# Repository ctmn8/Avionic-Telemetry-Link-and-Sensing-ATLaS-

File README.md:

# Avionic-Telemetry-Link-and-Sensing-ATLaS-
All-in-one telemetry system designed for rocketry.

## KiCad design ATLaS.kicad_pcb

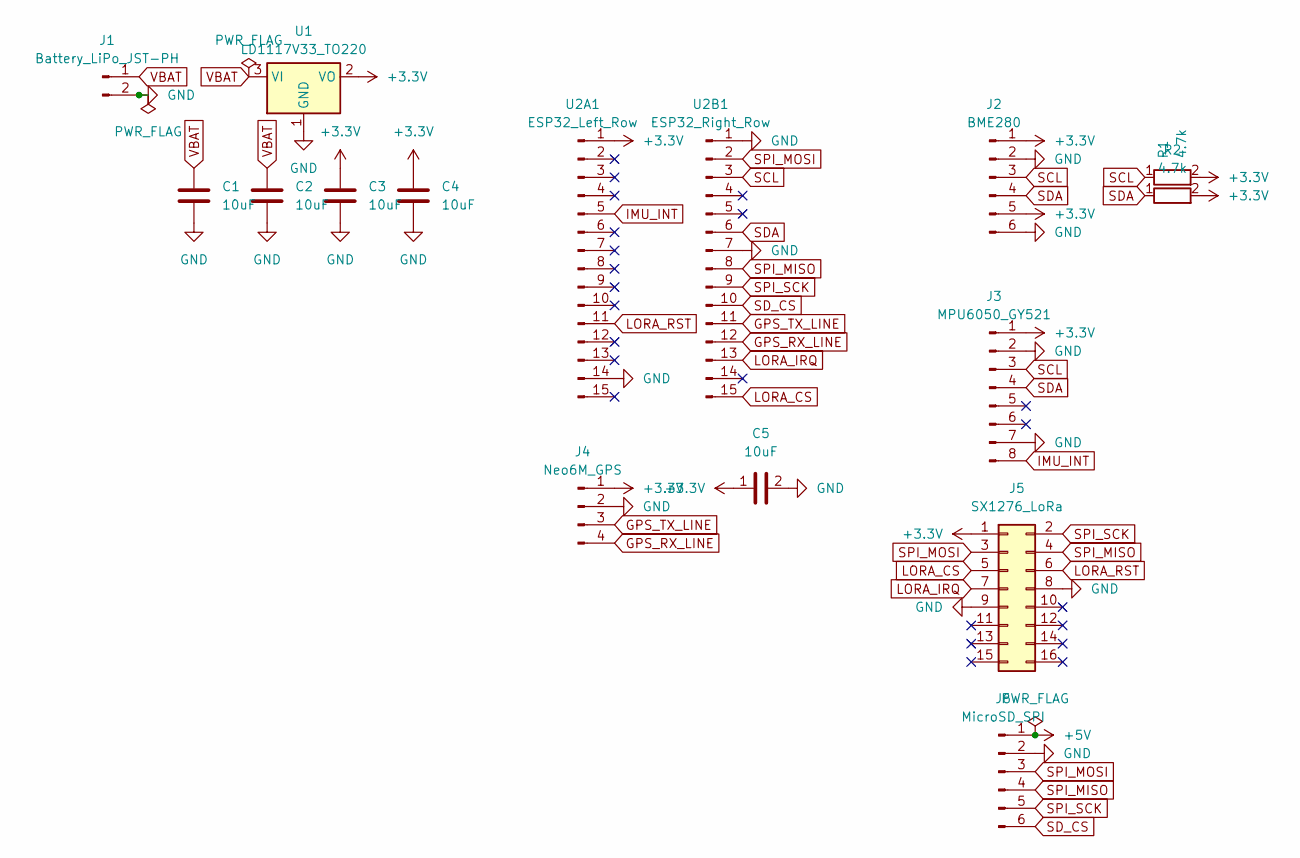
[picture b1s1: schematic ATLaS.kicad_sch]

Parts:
C1, C2, C3, C4, C5: 10uF; CP_Radial_D5.0mm_P2.50mm
J1: Battery_LiPo_JST-PH; JST_PH_S2B-PH-K_1x02_P2.00mm_Horizontal
J2: BME280; PinHeader_1x06_P2.54mm_Vertical
J3: MPU6050_GY521; PinHeader_1x08_P2.54mm_Vertical
J4: Neo6M_GPS; PinHeader_1x06_P2.54mm_Vertical
J5: SX1276_LoRa; PinHeader_2x08_P2.54mm_Vertical
J6: MicroSD_SPI; PinHeader_1x06_P2.54mm_Vertical
R1, R2: 4.7k; R_Axial_DIN0204_L3.6mm_D1.6mm_P7.62mm_Horizontal
U1: LD1117V33_TO220; TO-220-3_Vertical
U2A1: ESP32_Left_Row; PinHeader_1x15_P2.54mm_Vertical
U2B1: ESP32_Right_Row; PinHeader_1x15_P2.54mm_Vertical

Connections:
+3.3V: C3.1, C4.1, C5.1, J2.1, J2.5, J3.1, J4.1, J5.1, R1.2, R2.2, U1.2 (VO), U2A1.1
+5V: J6.1
GND: C1.2, C2.2, C3.2, C4.2, C5.2, J1.2, J2.2, J2.6, J3.2, J3.7, J4.2, J5.8, J5.9, J6.2, U1.1 (GND), U2A1.14, U2B1.1, U2B1.7
GPS_RX_LINE: J4.4, U2B1.12
GPS_TX_LINE: J4.3, U2B1.11
IMU_INT: J3.8, U2A1.5
LORA_CS: J5.5, U2B1.15
LORA_IRQ: J5.7, U2B1.13
LORA_RST: J5.6, U2A1.11
SCL: J2.3, J3.3, R1.1, U2B1.3
SDA: J2.4, J3.4, R2.1, U2B1.6
SD_CS: J6.6, U2B1.10
SPI_MISO: J5.4, J6.4, U2B1.8
SPI_MOSI: J5.3, J6.3, U2B1.2
SPI_SCK: J5.2, J6.5, U2B1.9
VBAT: C1.1, C2.1, J1.1, U1.3 (VI)

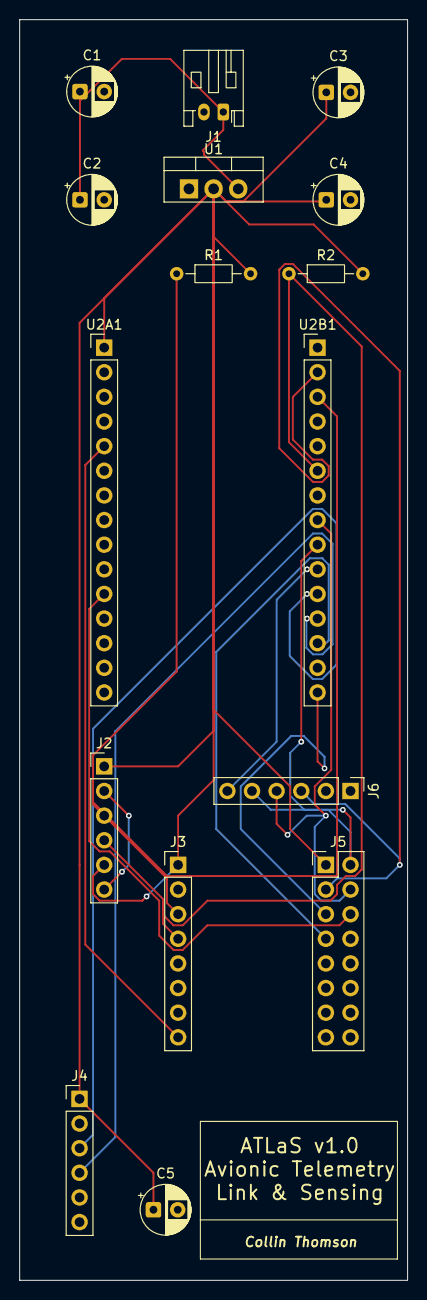
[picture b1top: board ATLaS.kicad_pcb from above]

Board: 2 copper layers, 40.0 x 130.0 mm, 16 parts (0 on the bottom side), 15 nets.
